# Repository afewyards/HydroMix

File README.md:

# ValveController

A mains-powered, Zigbee-connected controller for a hydronic **3-way mixing valve** — it
regulates the supply-water temperature of a floor heating/cooling system and keeps
regulating **autonomously** if the Zigbee link goes down.

One repo, three parts: a custom KiCad PCB (ESP32-C6), ESP-IDF firmware with a
host-testable control core, and a Zigbee2MQTT converter.

> **Status:** Firmware **1.7.0** released and OTA-deployed (2026-08-11); pure-C control core
> passes host-side unit tests; on-target bring-up of this board per
> [`firmware/BENCH_CHECKLIST.md`](firmware/BENCH_CHECKLIST.md) once assembled.
> PCB rev A — layout complete and **fab-ready** (4-layer, 100 % routed, DRC clean); boards
> ordered 2026-08-12. Personal project.

## What it does

A 3-way valve mixes **SOURCE** water (the hot or cold secondary side of a heat exchanger)
with **RETURN** water from the floor loop to produce **SUPPLY** water at a target
temperature. The controller:

- **Auto-detects mode** (heating / cooling / idle) from a heat-exchanger inlet sensor — the
  host never has to tell it which season it is.
- Regulates supply temperature with a **feed-forward mixing model + PI trim**, hard-bounded
  to floor-safe limits (17–35 °C).
- Drives an ESBE ARA661 230 V 3-point actuator through two solid-state (opto-triac) channels.
- Reads **5× DS18B20** probes (supply, return, source, and two heat-exchanger points) over 1-Wire.
- Exposes everything over **Zigbee** (Router role) for monitoring, tuning, the
  regulation-enable toggle, and **OTA** — with a first-class **Home Assistant / Zigbee2MQTT**
  integration.
- **Runs fully standalone** when Zigbee is unavailable, with a supply "governor" that
  de-escalates any temperature excursion toward safe recirculation regardless of mode.

### ⚠️ The counter-intuitive safety rule

Valve position **0 % = full recirculation** (return water only — thermally harmless).
**100 % = full source** (full hot or cold). Parking the valve "closed" (100 %) would run the
floor at full source temperature and is **dangerous** — so the safe park/idle position is
**mid-travel (~50 %)**, and a resync always drives toward the 0 % end, never the source end.
See the [design spec](docs/superpowers/specs/2026-07-13-firmware-design.md) for the full rationale.

## Hardware

Custom single-board design in KiCad (`pcb/`). Rev A highlights:

| Block | Parts |
|---|---|
| MCU | **ESP32-C6-WROOM-1-N4** (RISC-V, 802.15.4 Zigbee radio, 4 MB flash) |
| Power | 230 V AC → **Mean Well IRM-03-5** (5 V) → **TLV75733** LDO (3.3 V); USB-C 5 V is diode-OR'd in (B5819W) so the board bench-powers and flashes over USB-C with **no mains** |
| Pump interface | **TPS61040** boost to 24 V, driving a **Wilo Para ST 15-7-50 iPWM2** circulator over its PWM/feedback interface |
| Valve drive | 2× channel: **MOC3063S** zero-cross opto-triac → **Z0103MN** triac, switching the 230 V 3-point actuator; RC snubbers + X2 safety caps |
| AUX outputs | 2× **CPC1035N** PhotoMOS channels (24 VAC) with **HCPL-354** loop-open/short detection |
| Mains protection | Varistor (B72210S) + fuse |
| Sensing | 5× **DS18B20** on dedicated 1-Wire connectors (4.7 k pull-ups) |
| I/O | Tactile button, 8×8 LED matrix (**KWM-20881AGB** + **IS31FL3730** driver), **USB-C** — native USB-Serial-JTAG (power, flash, console, JTAG in one port) |
| Connectors | Phoenix pluggable terminal blocks (mains in, actuator) + 5 sensor headers |

Full parts list: [`pcb/ValveController.csv`](pcb/ValveController.csv). Custom 3D component models
live in `pcb/3dmodels/`; `board.step` (repo root) is the assembled-board export.

## Firmware

ESP-IDF 5.5.x, plain C on FreeRTOS. See **[`firmware/README.md`](firmware/README.md)** for the
full build/flash/monitor guide, GPIO map, partition/OTA scheme, console commands, and gestures.

The control logic lives in a **pure-C, IDF-free component** (`firmware/components/ctrl_core/`) so
it compiles and unit-tests on the host (macOS/Linux) before any hardware is involved:

- `feedforward` — exact mixing physics, `(T_set − T_return) / (T_source − T_return)`
- `pi` — PI trim with conditional anti-windup
- `governor` — outermost safety stage; ramps toward recirculation on any supply excursion
- `mode_detect` — heating/cooling/idle with asymmetric dwell + hysteresis
- `degradation` — sensor-fault fallback ladder
- `pos_estimator`, `interlock`, `alarm`, `config_map`

The IDF-side glue (`firmware/main/`) wires that core to hardware: `sensors_hw`, `valve_hw`,
`zigbee`, `ota`, `ui`, `console`, `control_task`, `config`.

Quick start:

```bash
. ~/esp/esp-idf/export.sh
cd firmware
idf.py set-target esp32c6       # first time only
idf.py build
idf.py -p <PORT> flash monitor  # over USB-C; Ctrl+] to exit the monitor
```

Host-side control tests (plain CMake + Unity, no hardware): [`firmware/test_host/`](firmware/test_host/).

## Zigbee / Home Assistant

Router role · manufacturer `Knife` · model `HydroMix`.

- **EP1** — Basic, Identify, On/Off (`water_running` = regulation enable, driven by the host's
  pump/flow automation), Thermostat (local temp = supply; setpoints clamped 17–35 °C; mode is
  auto-detected, host `SystemMode` writes accepted-but-ignored), Analog Output (manual position,
  writable only while regulation is off), OTA client, and a manufacturer-specific cluster
  (`0xFC00`) exposing ~10 tunables, a self-clearing `resync`, and read-only alarm/fault bitmaps.
- **EP2–EP6** — Temperature Measurement for supply, return, source, HX-A, HX-B.

[`z2m/valvectl.mjs`](z2m/valvectl.mjs) is the external Zigbee2MQTT converter (friendly entity names,
tunables as settings, alarms as binary sensors, OTA index). The manufacturer OTA-publishing steps
are documented in the comment header of that file.

## Repository layout

```
ValveController/
├── pcb/                        KiCad project (schematic, board, DRC rules, BOM)
│   ├── 3dmodels/               custom STEP models
│   ├── Kleist2.pretty/         project footprint library
│   └── backups/                local pre-edit snapshots (git-ignored)
├── firmware/                   ESP-IDF application
│   ├── main/                   IDF glue (sensors, valve, zigbee, ota, ui, console)
│   ├── components/ctrl_core/   pure-C control logic (host-testable)
│   └── test_host/              Unity unit tests
├── z2m/valvectl.mjs             Zigbee2MQTT external converter
├── docs/superpowers/           design spec + implementation plan
├── analysis/                   design review reports (schematic, PCB layout)
└── board.step                  assembled-board 3D export
```

## Safety

⚠️ This board switches **230 V AC mains**. All bench work — firmware, sensor reads, triac-drive
verification — can be done on **USB-C power alone**; do not connect mains until the drive channels
are verified per [`firmware/BENCH_CHECKLIST.md`](firmware/BENCH_CHECKLIST.md). And keep the position
convention in mind: the safe idle is **mid-travel**, not "closed."

## Documentation

- [Firmware guide](firmware/README.md) — build, GPIO map, OTA, console, gestures
- [Design spec](docs/superpowers/specs/2026-07-13-firmware-design.md) — control theory, safety, Zigbee model
- [Implementation plan](docs/superpowers/plans/2026-07-13-firmware.md)
- [Bench checklist](firmware/BENCH_CHECKLIST.md)
- [Design review — schematic, 2026-08-11](analysis/design_review_2026-08-11.md)
- [Design review — PCB layout, 2026-08-12](analysis/design_review_2026-08-12_pcb.md) — fab-ready verdict; mains isolation verified against IEC 60664-1

---

Personal project by Thierry Kleist. Released under the [MIT License](LICENSE).

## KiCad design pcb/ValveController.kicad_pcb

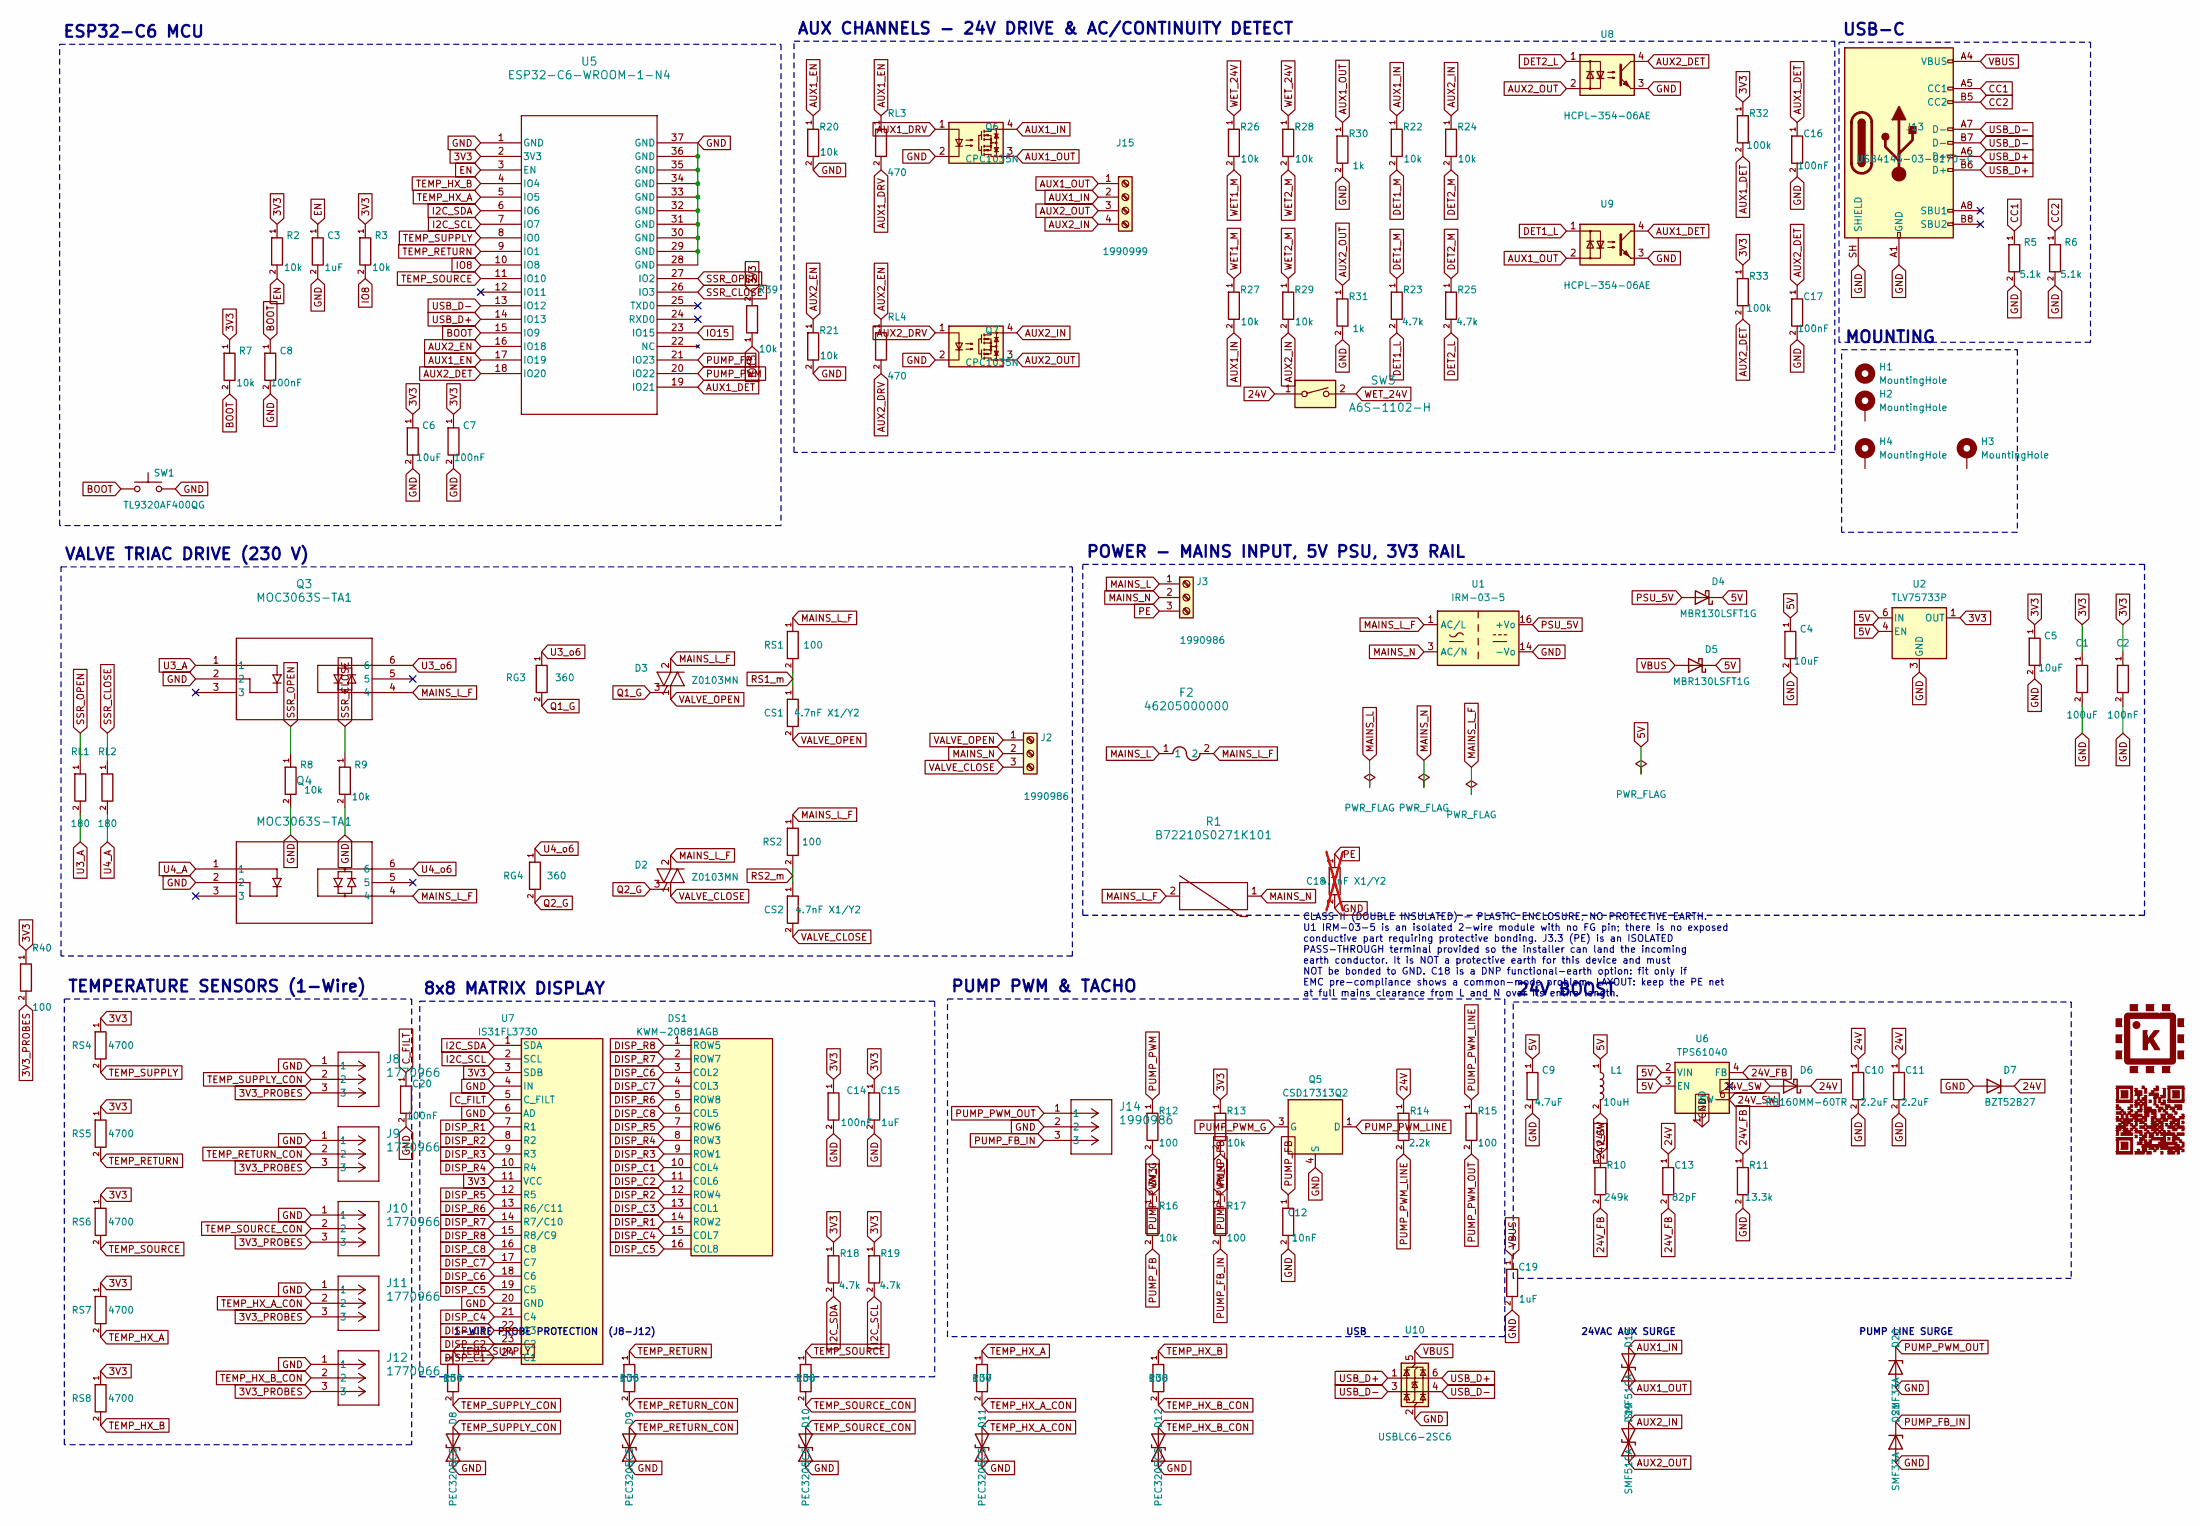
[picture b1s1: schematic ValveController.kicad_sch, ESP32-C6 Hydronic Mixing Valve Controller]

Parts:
C1: 100uF; C_1210_3225Metric; MPN CL32A107MQVNNNE
C2, C7, C8, C14, C16, C17, C20: 100nF; C_0402_1005Metric; MPN CL05B104KO5NNNC
C3, C15, C19: 1uF; C_0402_1005Metric; MPN CL05A105KP5NNNC
C4, C5, C6: 10uF; C_0805_2012Metric; MPN C0805C106K3PACTU
C9: 4.7uF; C_0805_2012Metric; MPN GRM21BR71C475KE51K
C10, C11: 2.2uF; C_1206_3216Metric; MPN GCM31CR71H225KA55L
C12: 10nF; C_0402_1005Metric; MPN C0402C103K5RECAUTO
C13: 82pF; C_0402_1005Metric; MPN GRM1555C1H820JA01D
C18: 4.7nF X1/Y2; C_Rect_L13.0mm_W5.0mm_P10.00mm_FKS3_FKP3_MKS4; MPN R413F147050T1K; not fitted
CS1, CS2: 4.7nF X1/Y2; C_Rect_L13.0mm_W5.0mm_P10.00mm_FKS3_FKP3_MKS4; MPN R413F147050T1K
D2, D3: Z0103MN; SOT-223; MPN Z0103MN 5AA4
D4, D5: MBR130LSFT1G; D_SOD-123F; MPN MBR130LSFT1G
D6: RB160MM-60TR; D_SOD-123F; MPN RB160MM-60TR
D7: BZT52B27; D_SOD-123F; MPN BZT52B27
D8, D9, D10, D11, D12: PEC3205CS; D_SOD-323F; MPN PEC3205CS_R1_00701
D18, D19: SMF51CA; D_SOD-123F; MPN SMF51CA
D20, D21: SMF33A; D_SOD-123F; MPN SMF33A
DS1: KWM-20881AGB; LED_Matrix_8x8_20mm; MPN KWM-20881AGB
F2: 46205000000; Fuse_Littelfuse-NANO2-462; MPN 46205000000
G1: KleistLabs_Logo_8mm_Copper
G2: QR_HydroMix_SilkOnDark; QR_HydroMix_250um_SilkOnDark
H1, H2, H3, H4: MountingHole; MountingHole_3.2mm_M3_ISO7380
J2, J3, J14: 1990986; TerminalBlock_Phoenix_SPT-2,5-3-H-5.0_1x03_P5.00mm_Horizont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; MPN 1990986
J8, J9, J10, J11, J12: 1770966; TerminalBlock_Phoenix_PTSM-0,5-3-2.5-V-THR_1x03_P2.50mm_Ver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; MPN 1770966
J13: USB4145-03-0170-C; USB_C_Receptacle_GCT_USB4145-03-0170-C_Vertical_SMT; MPN USB4145-03-0170-C
J15: 1990999; TerminalBlock_Phoenix_SPT-2,5-4-H-5.0_1x04_P5.00mm_Horizont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; MPN 1990999
L1: 10uH; L_Taiyo-Yuden_NR-40xx; MPN LSXND4040TKL100MDG
Q3, Q4: MOC3063S-TA1; MOC306XS_LTO-L; MPN MOC3063S-TA1
Q5: CSD17313Q2; MPN CSD17313Q2
Q6, Q7: CPC1035N; SOP-4_3.8x4.1mm_P2.54mm; MPN CPC1035NTR
R1: B72210S0271K101; RV_Disc_D12mm_W5.4mm_P7.5mm; MPN B72210S0271K101
R2, R3, R7, R8, R9, R13, R16, R20, R21, R22, R24, R26, R27, R28, R29, R39: 10k; R_0402_1005Metric; MPN AC0402FR-0710KL
R5, R6: 5.1k; R_0402_1005Metric; MPN RC0402FR-075K1L
R10: 249k; R_0402_1005Metric; MPN RC0402FR-07249KL
R11: 13.3k; R_0402_1005Metric; MPN RC0402FR-0713K3L
R12, R34, R35, R36, R37, R38: 100; R_0402_1005Metric; MPN RC0402FR-07100RL
R14: 2.2k; R_1206_3216Metric; MPN ERJ-P08J222V
R15, R17, R40: 100; R_1206_3216Metric; MPN ERJ-P08J101V
R18, R19, R23, R25: 4.7k; R_0402_1005Metric; MPN RC0402FR-074K7L
R30, R31: 1k; R_0402_1005Metric; MPN user stock (1k 0402)
R32, R33: 100k; R_0402_1005Metric; MPN RC0402FR-07100KL
RG3, RG4: 360; R_0603_1608Metric; MPN RC0603FR-07360RL
RL1, RL2: 180; R_0402_1005Metric; MPN RC0402FR-07180RL
RL3, RL4: 470; R_0402_1005Metric; MPN RC0402FR-07470RL
RS1, RS2: 100; R_1206_3216Metric; MPN ERJ-P08J101V
RS4, RS5, RS6, RS7, RS8: 4700; R_0402_1005Metric; MPN RC0402FR-074K7L
SW1: TL9320AF400QG; SW_SPST_TL9320; MPN TL9320AF400QG
SW3: A6S-1102-H; SW_DIP_SPSTx01_Slide_Omron_A6S-110x_W8.9mm_P2.54mm; MPN A6S-1102-H
U1: IRM-03-5; Converter_ACDC_MeanWell_IRM-03-xx_THT; MPN IRM-03-5
U2: TLV75733P; WSON-6-1EP_2x2mm_P0.65mm_EP1x1.6mm_ThermalVias; MPN TLV75733PDRVR
U5: ESP32-C6-WROOM-1-N4; MOD28_ESP32-C6-WROOM-1_EXP; MPN ESP32-C6-WROOM-1-N4
U6: TPS61040; WSON-6-1EP_2x2mm_P0.65mm_EP1x1.6mm_ThermalVias; MPN TPS61040DRVR
U7: IS31FL3730; QFN-24-1EP_4x4mm_P0.5mm_EP2.5x2.5mm; MPN IS31FL3730-QFLS2-TR
U8, U9: HCPL-354-06AE; SO-4_4.4x3.6mm_P2.54mm; MPN HCPL-354-06AE
U10: USBLC6-2SC6; SOT-23-6; MPN USBLC6-2SC6

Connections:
3V3: C1.1, C2.1, C5.1, C6.1, C7.1, C14.1, C15.1, R2.1, R3.1, R7.1, R13.1, R16.1, R18.1, R19.1, R32.1, R33.1, R39.2, R40.1, RS4.1, RS5.1, RS6.1, RS7.1, RS8.1, U2.1 (OUT), U5.2 (3V3), U7.3 (SDB), U7.11 (VCC)
3V3_PROBES: J8.3, J9.3, J10.3, J11.3, J12.3, R40.2
5V: C4.1, C9.1, D4.1 (K), D5.1 (K), L1.1, U2.4 (EN), U2.6 (IN), U6.2 (VIN), U6.3 (EN)
24V: C10.1, C11.1, C13.1, D6.1 (K), D7.1 (K), R10.1, R14.1, SW3.1
24V_FB: C13.2, R10.2, R11.1, U6.4 (FB)
24V_SW: D6.2 (A), L1.2, U6.6 (SW)
AUX1_DET: C16.1, R32.2, U5.19 (IO21), U9.4
AUX1_DRV: Q6.1, RL3.2
AUX1_EN: R20.1, RL3.1, U5.17 (IO19)
AUX1_IN: D18.2 (A2), J15.2, Q6.4, R22.1, R27.2
AUX1_OUT: D18.1 (A1), J15.1, Q6.3, R30.1, U9.2
AUX2_DET: C17.1, R33.2, U5.18 (IO20), U8.4
AUX2_DRV: Q7.1, RL4.2
AUX2_EN: R21.1, RL4.1, U5.16 (IO18)
AUX2_IN: D19.2 (A2), J15.4, Q7.4, R24.1, R29.2
AUX2_OUT: D19.1 (A1), J15.3, Q7.3, R31.1, U8.2
BOOT: C8.1, R7.2, SW1.1, U5.15 (IO9)
CC1: J13.A5 (CC1), R5.1
CC2: J13.B5 (CC2), R6.1
C_FILT: C20.1, U7.5 (C_FILT)
DET1_L: R23.2, U9.1
DET1_M: R22.2, R23.1
DET2_L: R25.2, U8.1
DET2_M: R24.2, R25.1
DISP_C1: DS1.10 (COL4), U7.24 (C1)
DISP_C2: DS1.11 (COL6), U7.23 (C2)
DISP_C3: DS1.13 (COL1), U7.22 (C3)
DISP_C4: DS1.15 (COL7), U7.21 (C4)
DISP_C5: DS1.16 (COL8), U7.19 (C5)
DISP_C6: DS1.3 (COL2), U7.18 (C6)
DISP_C7: DS1.4 (COL3), U7.17 (C7)
DISP_C8: DS1.6 (COL5), U7.16 (C8)
DISP_R1: DS1.14 (ROW2), U7.7 (R1)
DISP_R2: DS1.12 (ROW4), U7.8 (R2)
DISP_R3: DS1.9 (ROW1), U7.9 (R3)
DISP_R4: DS1.8 (ROW3), U7.10 (R4)
DISP_R5: DS1.7 (ROW6), U7.12 (R5)
DISP_R6: DS1.5 (ROW8), U7.13 (R6/C11)
DISP_R7: DS1.2 (ROW7), U7.14 (R7/C10)
DISP_R8: DS1.1 (ROW5), U7.15 (R8/C9)
EN: C3.1, R2.2, U5.3 (EN)
GND: C1.2, C2.2, C3.2, C4.2, C5.2, C6.2, C7.2, C8.2, C9.2, C10.2, C11.2, C12.2, C14.2, C15.2, C16.2, C17.2, C18.2, C19.2, C20.2, D7.2 (A), D8.1 (A1), D9.1 (A1), D10.1 (A1), D11.1 (A1), D12.1 (A1), D20.2 (A), D21.2 (A), J8.1, J9.1, J10.1, J11.1, J12.1, J13.A1 (GND), J13.A12 (GND), J13.B1 (GND), J13.B12 (GND), J13.SH (SHIELD), J14.2, Q3.2, Q4.2, Q5.4 (S), Q5.7 (S), Q6.2, Q7.2, R5.2, R6.2, R8.2, R9.2, R11.2, R20.2, R21.2, R30.2, R31.2, SW1.2, U1.14 (-Vo), U2.3 (GND), U2.7 (GND), U5.1 (GND), U5.28 (GND), U5.29 (GND), U5.30 (GND), U5.31 (GND), U5.32 (GND), U5.33 (GND), U5.34 (GND), U5.35 (GND), U5.36 (GND), U5.37 (GND), U6.1 (GND), U6.7 (GND), U7.4 (IN), U7.6 (AD), U7.20 (GND), U7.25 (GND), U8.3, U9.3, U10.2 (GND)
I2C_SCL: R19.2, U5.7 (IO7), U7.2 (SCL)
I2C_SDA: R18.2, U5.6 (IO6), U7.1 (SDA)
IO8: R3.2, U5.10 (IO8)
IO15: R39.1, U5.23 (IO15)
MAINS_L: F2.1, J3.1
MAINS_L_F: D2.2 (A2), D2.4 (A4), D3.2 (A2), D3.4 (A4), F2.2, Q3.4, Q4.4, R1.2, RS1.1, RS2.1, U1.1 (AC/L)
MAINS_N: J2.2, J3.2, R1.1, U1.3 (AC/N)
PE: C18.1, J3.3
PSU_5V: D4.2 (A), U1.16 (+Vo)
PUMP_FB: C12.1, R16.2, R17.1, U5.21 (IO23)
PUMP_FB_IN: D21.1 (K), J14.3, R17.2
PUMP_PWM: R12.1, U5.20 (IO22)
PUMP_PWM_G: Q5.3 (G), R12.2, R13.2
PUMP_PWM_LINE: Q5.1 (D), Q5.2 (D), Q5.5 (D), Q5.6 (D), Q5.8 (D), R14.2, R15.1
PUMP_PWM_OUT: D20.1 (K), J14.1, R15.2
Q1_G: D3.3 (G), RG3.2
Q2_G: D2.3 (G), RG4.2
RS1_m: CS1.1, RS1.2
RS2_m: CS2.1, RS2.2
SSR_CLOSE: R9.1, RL2.1, U5.26 (IO3)
SSR_OPEN: R8.1, RL1.1, U5.27 (IO2)
TEMP_HX_A: R37.1, RS7.2, U5.5 (IO5)
TEMP_HX_A_CON: D11.2 (A2), J11.2, R37.2
TEMP_HX_B: R38.1, RS8.2, U5.4 (IO4)
TEMP_HX_B_CON: D12.2 (A2), J12.2, R38.2
TEMP_RETURN: R35.1, RS5.2, U5.9 (IO1)
TEMP_RETURN_CON: D9.2 (A2), J9.2, R35.2
TEMP_SOURCE: R36.1, RS6.2, U5.11 (IO10)
TEMP_SOURCE_CON: D10.2 (A2), J10.2, R36.2
TEMP_SUPPLY: R34.1, RS4.2, U5.8 (IO0)
TEMP_SUPPLY_CON: D8.2 (A2), J8.2, R34.2
U3_A: Q3.1, RL1.2
U3_o6: Q3.6, RG3.1
U4_A: Q4.1, RL2.2
U4_o6: Q4.6, RG4.1
USB_D+: J13.A6 (D+), J13.B6 (D+), U5.14 (IO13), U10.1 (I/O1), U10.6 (I/O1)
USB_D-: J13.A7 (D-), J13.B7 (D-), U5.13 (IO12), U10.3 (I/O2), U10.4 (I/O2)
VALVE_CLOSE: CS2.2, D2.1 (A1), J2.3
VALVE_OPEN: CS1.2, D3.1 (A1), J2.1
VBUS: C19.1, D5.2 (A), J13.A4 (VBUS), J13.A9 (VBUS), J13.B4 (VBUS), J13.B9 (VBUS), U10.5 (VBUS)
WET1_M: R26.2, R27.1
WET2_M: R28.2, R29.1
WET_24V: R26.1, R28.1, SW3.2

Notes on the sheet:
CLASS II (DOUBLE INSULATED) - PLASTIC ENCLOSURE, NO PROTECTIVE EARTH. U1 IRM-03-5 is an isolated 2-wire module with no FG pin; there is no exposed conductive part requiring protective bonding. J3.3 (PE) is an ISOLATED PASS-THROUGH terminal provided so the installer can land the incoming earth condu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
8x8 MATRIX DISPLAY
PUMP PWM & TACHO
24VAC AUX SURGE
24V BOOST
PUMP LINE SURGE
USB
AUX CHANNELS - 24V DRIVE & AC/CONTINUITY DETECT
1-WIRE PROBE PROTECTION (J8-J12)
MOUNTING
ESP32-C6 MCU
USB-C
TEMPERATURE SENSORS (1-Wire)
POWER - MAINS INPUT, 5V PSU, 3V3 RAIL
VALVE TRIAC DRIVE (230 V)

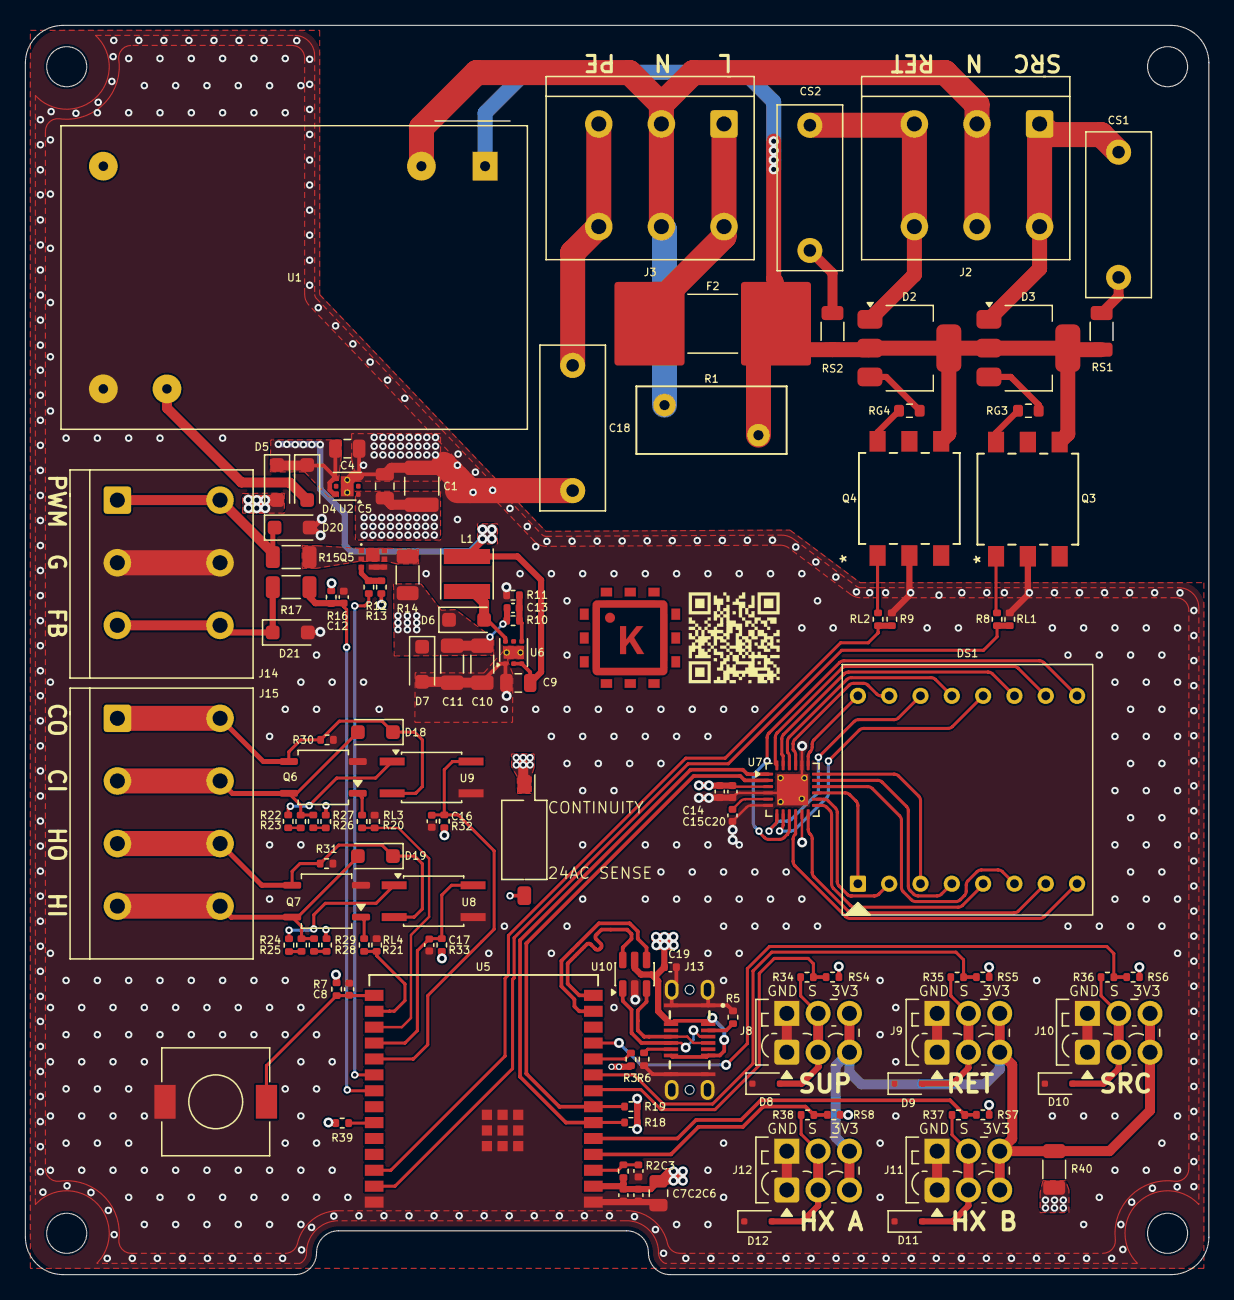
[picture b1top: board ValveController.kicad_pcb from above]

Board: 4 copper layers, 94.5 x 99.8 mm, 123 parts (0 on the bottom side), 85 nets.
